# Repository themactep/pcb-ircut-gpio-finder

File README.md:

# pcb-gpio-finder

Simple indicator of IRCUT signals for finding GPIO on an IPC.

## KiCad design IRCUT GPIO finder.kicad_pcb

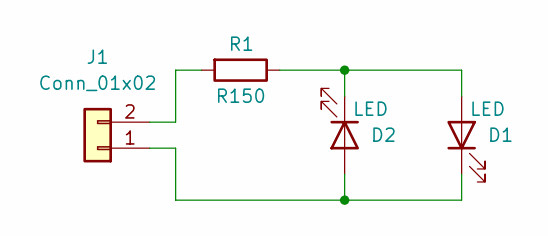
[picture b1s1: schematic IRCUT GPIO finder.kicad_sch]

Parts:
D1, D2: LED; LED_1206_3216Metric
J1: Conn_01x02; JST_GH_SM02B-GHS-TB_1x02-1MP_P1.25mm_Horizontal
R1: R150; R_1206_3216Metric

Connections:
unnamed: D1.2 (A), D2.1 (K), R1.1
unnamed: D1.1 (K), D2.2 (A), J1.1
unnamed: J1.2, R1.2

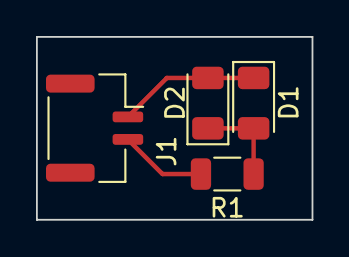
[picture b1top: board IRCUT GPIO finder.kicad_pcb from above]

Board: 2 copper layers, 15.3 x 10.2 mm, 4 parts (0 on the bottom side), 3 nets.
